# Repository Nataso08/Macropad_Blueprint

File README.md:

# Macropad_Blueprint
My personal macropad for Hack Club Blueprint

It contains a OLED display 0.91", a rotay encoder and a 3x4 keyboard matrix. The MCU is a RP2040 XIAO.

It's my first PCB & CAD project ever, and I liked do this. 

## Links:

- [Dashboard](https://blueprint.hackclub.com/home)
- [Tutorial (text)](https://blueprint.hackclub.com/hackpad)

## BOM
- 1x Seeed Studio XIAO RP2040
- 1x 0.91 inch OLED displays
- 1x EC11 Rotary encoder
- 12x MX-Style switches
- 12x 1N4148 Diodes
- 8x M3x5mx4mm heatset inserts
- 8x M3 Screws

## Images
### Schematic

### PCB

### PCB 3D render

### CAD
[The OnShape project](https://cad.onshape.com/documents/a87e2dd97fe0598f146e6970/w/66d04f377217749244a38da7/e/cb98773740db47e258a91458)
#### Full CAD

#### Only bottom

#### Only main

#### Only knob

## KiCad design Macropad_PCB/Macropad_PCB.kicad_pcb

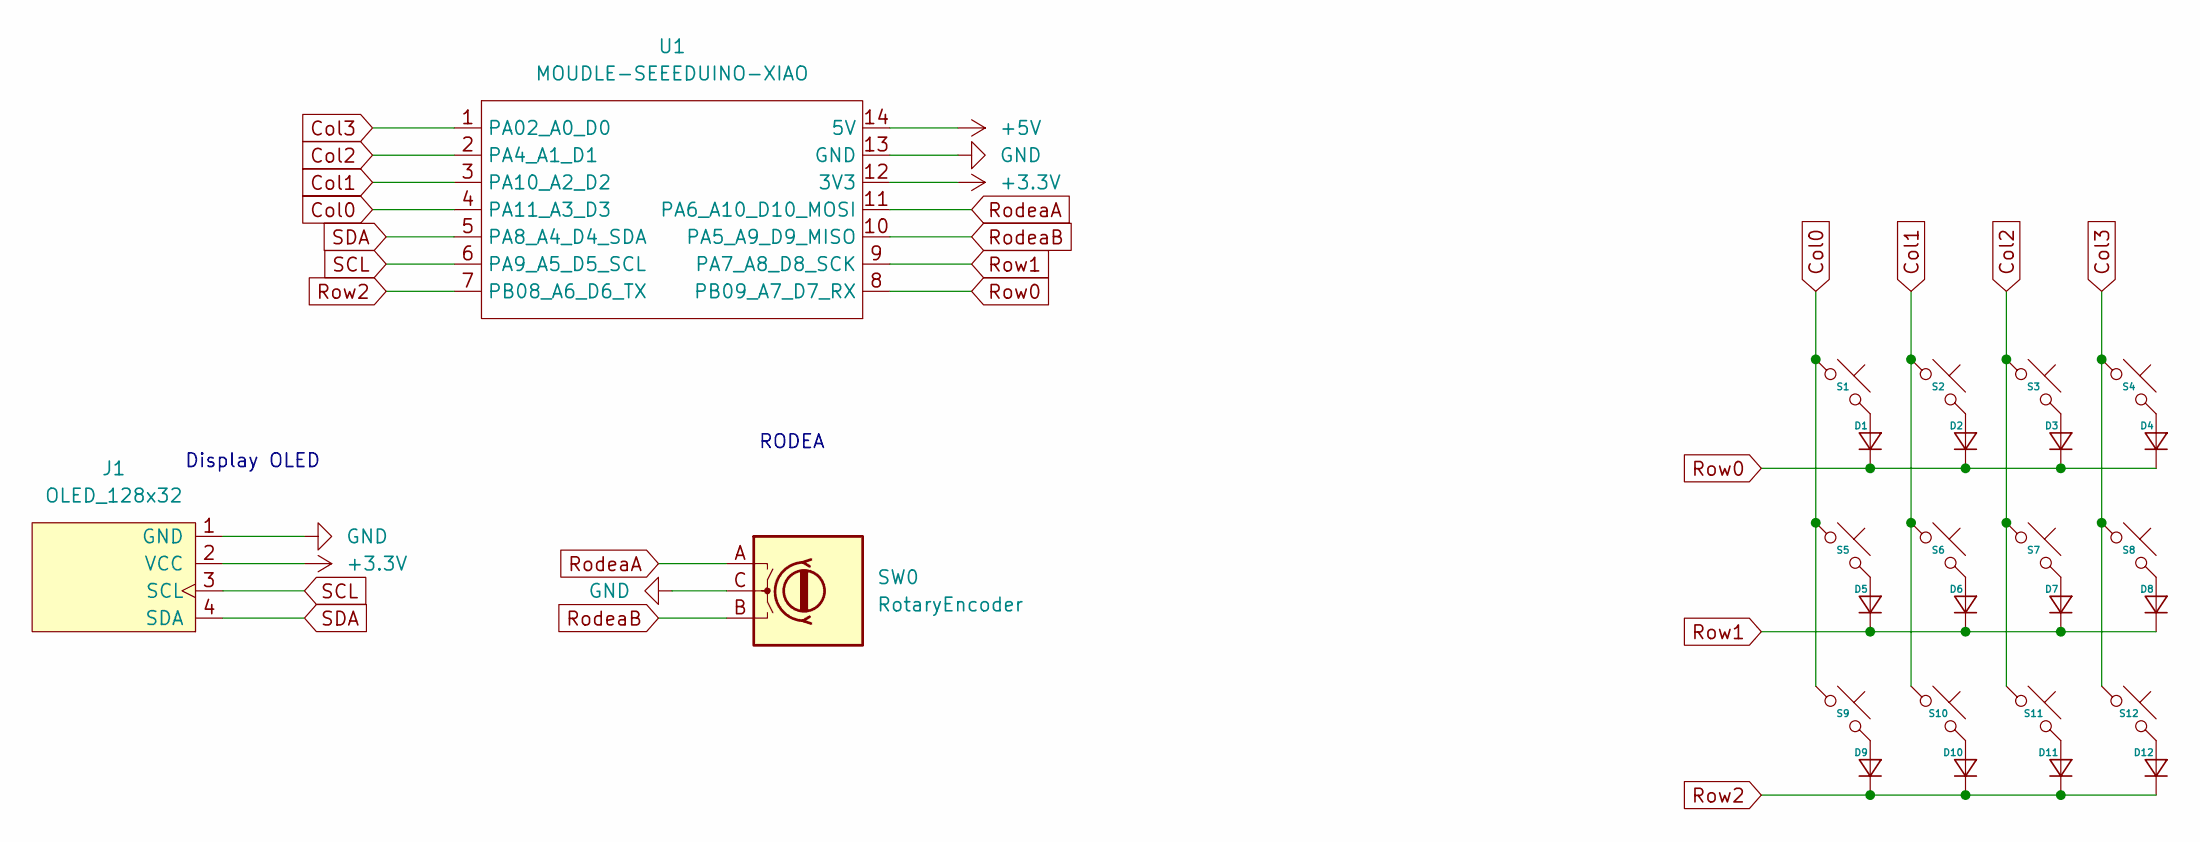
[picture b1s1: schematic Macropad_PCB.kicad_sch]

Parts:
D1, D2, D3, D4, D5, D6, D7, D8, D9, D10, D11, D12: D_DO-35_SOD27_P7.62mm_Horizontal
J1: OLED_128x32
S1, S2, S3, S4, S5, S6, S7, S8, S9, S10, S11, S12: MX_PCB_1.00u
SW0: RotaryEncoder; RotaryEncoder_Alps_EC11E-Switch_Vertical_H20mm
U1: MOUDLE-SEEEDUINO-XIAO; XIAO-Generic-Hybrid-14P-2.54-21X17.8MM

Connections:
+3.3V: J1.2 (VCC), U1.12 (3V3)
+5V: U1.14 (5V)
Col0: S1.1, S5.1, S9.1, U1.4 (PA11_A3_D3)
Col1: S2.1, S6.1, S10.1, U1.3 (PA10_A2_D2)
Col2: S3.1, S7.1, S11.1, U1.2 (PA4_A1_D1)
Col3: S4.1, S8.1, S12.1, U1.1 (PA02_A0_D0)
GND: J1.1 (GND), SW0.C, U1.13 (GND)
unnamed: D1.2 (A), S1.2
unnamed: D2.2 (A), S2.2
unnamed: D3.2 (A), S3.2
unnamed: D4.2 (A), S4.2
unnamed: D5.2 (A), S5.2
unnamed: D6.2 (A), S6.2
unnamed: D7.2 (A), S7.2
unnamed: D8.2 (A), S8.2
unnamed: D9.2 (A), S9.2
unnamed: D10.2 (A), S10.2
unnamed: D11.2 (A), S11.2
unnamed: D12.2 (A), S12.2
RodeaA: SW0.A, U1.11 (PA6_A10_D10_MOSI)
RodeaB: SW0.B, U1.10 (PA5_A9_D9_MISO)
Row0: D1.1 (K), D2.1 (K), D3.1 (K), D4.1 (K), U1.8 (PB09_A7_D7_RX)
Row1: D5.1 (K), D6.1 (K), D7.1 (K), D8.1 (K), U1.9 (PA7_A8_D8_SCK)
Row2: D9.1 (K), D10.1 (K), D11.1 (K), D12.1 (K), U1.7 (PB08_A6_D6_TX)
SCL: J1.3 (SCL), U1.6 (PA9_A5_D5_SCL)
SDA: J1.4 (SDA), U1.5 (PA8_A4_D4_SDA)

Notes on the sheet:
Display OLED
RODEA

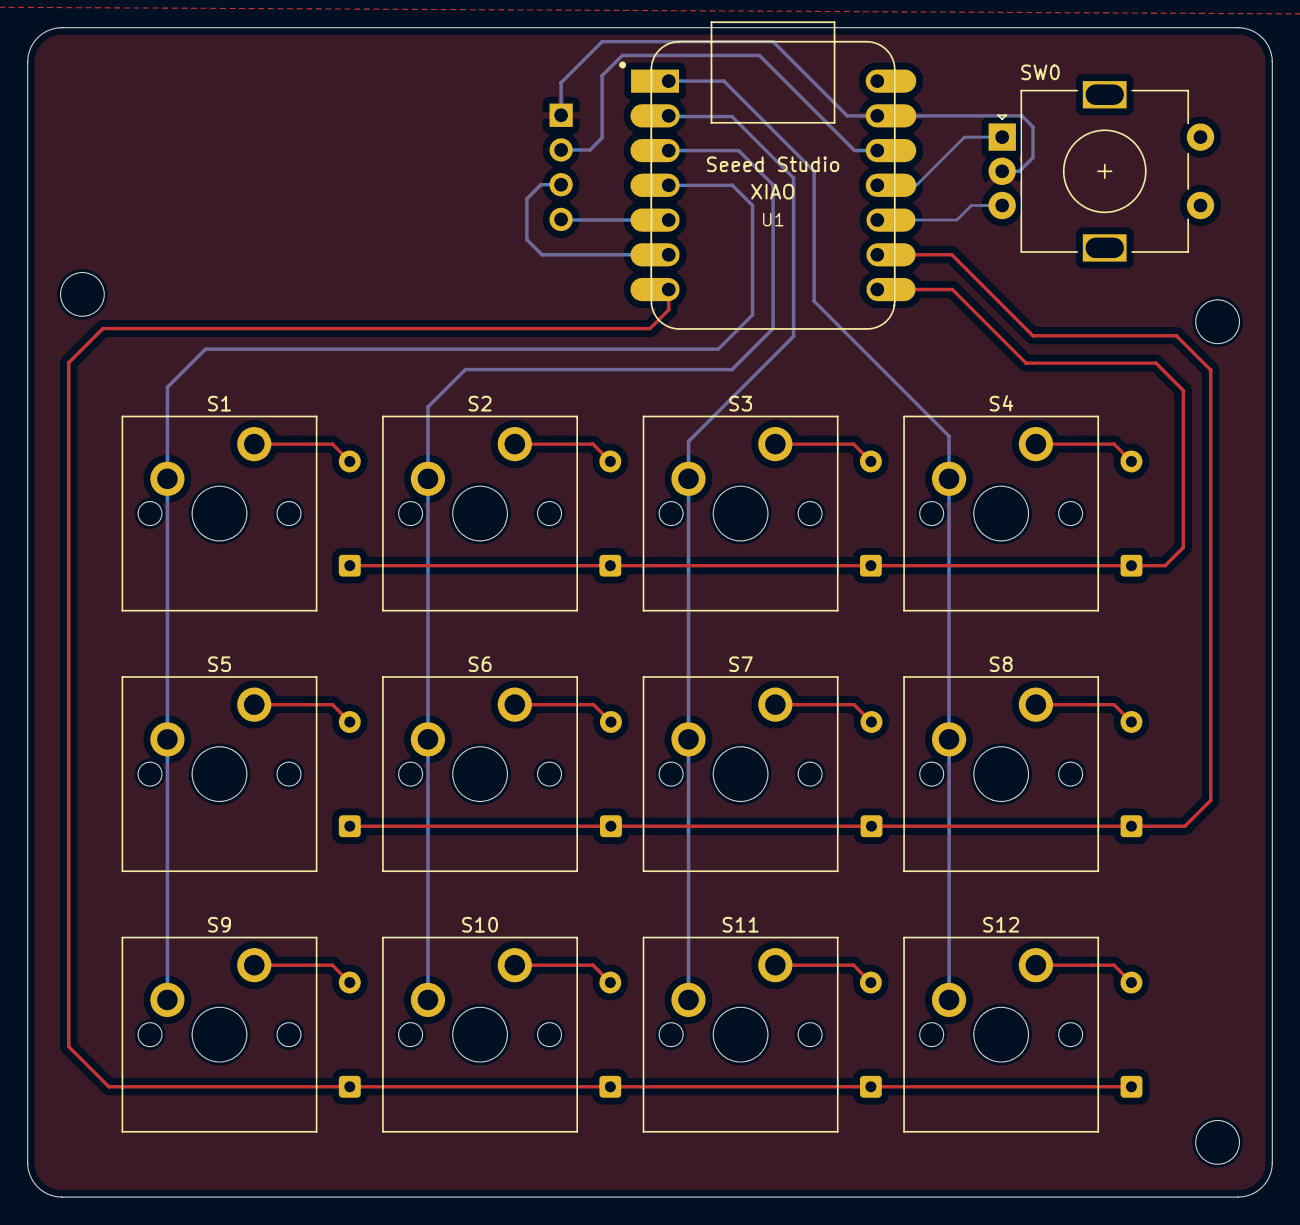
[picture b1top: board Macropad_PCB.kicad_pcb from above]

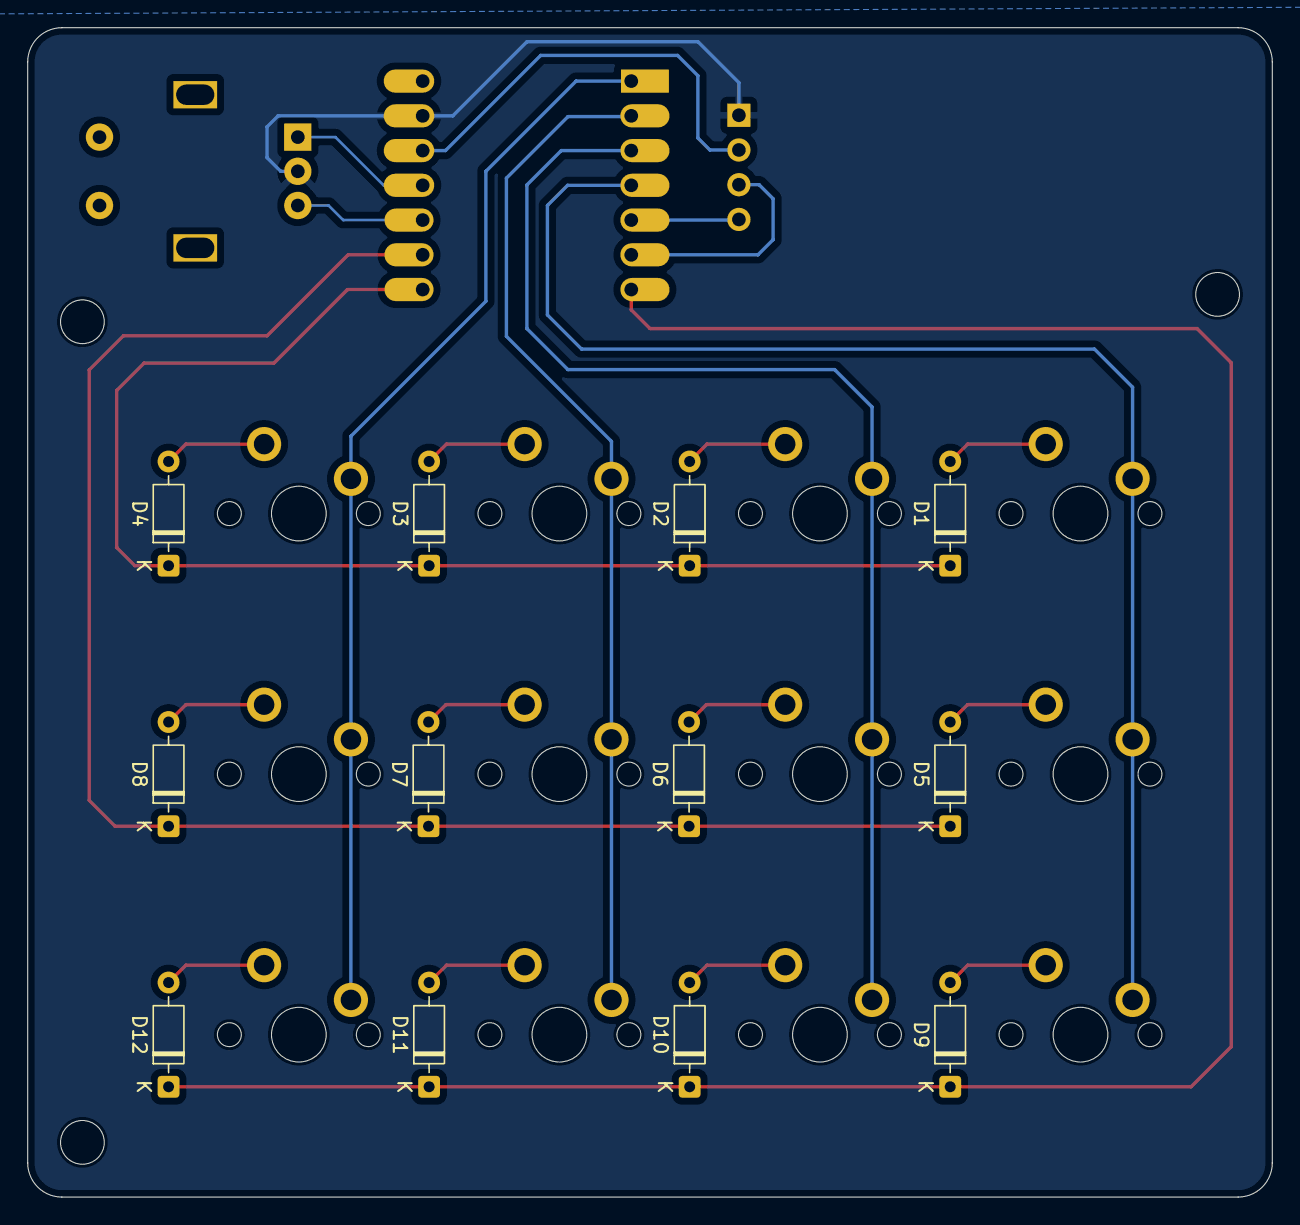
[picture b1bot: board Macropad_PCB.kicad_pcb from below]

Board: 2 copper layers, 91.0 x 85.5 mm, 27 parts (12 on the bottom side), 25 nets.

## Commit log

2026-03-13 Add links section to README
    Added links section to README
2026-03-13 Update links in README for Hack Club Blueprint
2026-03-13 Initialization KiCad project
2026-03-15 Fix formatting in README links section
2026-03-16 Project init
2026-03-16 Remove backups from repo
2026-03-16 Inizio PCB
2026-03-16 PCB. Ancora alcuni errori
2026-03-22 Diodes on PCB back
2026-03-24 Correzione errori CC
2026-03-30 Librerie macropad
2026-03-30 PCB finito (in teoria)
2026-03-30 Project exportation
2026-03-30 Aggiornamento file esportazione
2026-03-30 Aggiornamento export
2026-03-31 Update PCB
2026-03-31 STEP files and gembers
2026-03-31 CAD files
2026-03-31 Base firmware
2026-03-31 Update README with project details and BOM
    Added details about components and links for the macropad project.
2026-03-31 Add images for schematic, PCB, and CAD sections
    Added images for schematic, PCB, and CAD designs.
2026-03-31 Added filled zone
2026-03-31 Add PCB 3D render section to README
    Added a 3D render image of the PCB to the README.
2026-04-11 Modify OnShape project link in README
    Updated the OnShape project link to include render mode and UI state parameters.
2026-04-13 XIAO nel 3D
2026-04-13 Update image in README for CAD section
